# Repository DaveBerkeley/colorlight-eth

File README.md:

ColorLight Ethernet Interface
====

This PCB provides the RJ45 and magnetics to connect a pair of Ethernet sockets to the 
[Colorlight i9](https://github.com/wuxx/Colorlight-FPGA-Projects/blob/master/colorlight_i9_v7.2.md)
FPGA dev board.

I'm using the excellent [LiteX](https://github.com/enjoy-digital/litex) SoC builder from [Enjoy Digital](http://www.enjoy-digital.fr/).

This uses the 
[liteeth](https://github.com/enjoy-digital/liteeth)
library to create the MAC and interface to the PHY.

The dev board contains a pair of Broadcom 
[B50612D](https://github.com/wuxx/Colorlight-FPGA-Projects/blob/master/doc/B50612D-datasheet.pdf)
Gigabit Ethernet Transceivers.

The project was inspired by this [Ethernet interface](https://github.com/kazkojima/colorlight-i5-tips#ethernet) by kazkojima.

I found an 
[RJ45 connecter](https://www.digikey.co.uk/en/products/detail/trp-connector-b-v/2250013-4/9451594)
with built in magnetics, which makes the whole design a lot simpler.

I've got the system loading a binary image over TFTP and booting. I've not yet had time to do any more tests.

The edge connector does not have LED outputs on it unfortunately. 
So I've wired these to a 5-pin header on the side of the board.
There are 4 resistors on the back of the board to limit the current through the LEDs.
The LEDs in these sockets are bicolour bidirectional, but only one direction is supported.

There is also a jumper to select between 5V and 3V3 connection to the pulse transformers, 
but the circuit seems to work without this being conencted to either. 
I need to look into its purpose.

I'm currently running [PanglOS](https://github.com/DaveBerkeley/panglos) on the RISC-V.
This doesn't yet have a scheduler on the RISC-V, so I don't have any multitasking.
Software for the Ethernet interface on my board is still work in progess.

            __   _ __      _  __
           / /  (_) /____ | |/_/
          / /__/ / __/ -_)>  <
         /____/_/\__/\__/_/|_|
       Build your hardware, easily!

     (c) Copyright 2012-2024 Enjoy-Digital
     (c) Copyright 2007-2015 M-Labs

     BIOS built on Oct 19 2024 10:06:09
     BIOS CRC passed (bfabfcc0)

     LiteX git sha1: a59b67e4

    --=============== SoC ==================--
    CPU:            VexRiscv_LinuxDebug @ 50MHz
    BUS:            wishbone 32-bit @ 4GiB
    CSR:            32-bit data
    ROM:            128.0KiB
    SRAM:           8.0KiB
    L2:             8.0KiB
    FLASH:          8.0MiB
    SDRAM:          8.0MiB 32-bit @ 50MT/s (CL-2 CWL-2)
    MAIN-RAM:       8.0MiB

    --========== Initialization ============--
    Ethernet init...
    Initializing SDRAM @0x40000000...
    Switching SDRAM to software control.
    Switching SDRAM to hardware control.
    Memtest at 0x40000000 (2.0MiB)...
      Write: 0x40000000-0x40200000 2.0MiB     
       Read: 0x40000000-0x40200000 2.0MiB     
    Memtest OK
    Memspeed at 0x40000000 (Sequential, 2.0MiB)...
      Write speed: 18.4MiB/s
       Read speed: 25.3MiB/s

    Initializing w25q64 SPI Flash @0x00800000...
    SPI Flash clk configured to 25 MHz
    Memspeed at 0x800000 (Sequential, 4.0KiB)...
       Read speed: 2.3MiB/s
    Memspeed at 0x800000 (Random, 4.0KiB)...
       Read speed: 1.0MiB/s

    --============== Boot ==================--
    Booting from serial...
    Press Q or ESC to abort boot completely.
    sL5DdSMmkekro
                 Timeout
    Booting from flash...
    Error: Invalid image length 0xacc0d000
    Booting from network...
    Local IP: 192.168.0.249
    Remote IP: 192.168.0.189
    Booting from boot.json...
    Copying app.bin to 0x40000000... (109760 bytes)
    Executing booted program at 0x40000000

    --============= Liftoff! ===============--
     ____                   _  ___  ____  
    |  _ \ __ _ _ __   __ _| |/ _ \/ ___| 
    | |_) / _` | '_ \ / _` | | | | \___ \ 
    |  __/ (_| | | | | (_| | | |_| |___) |
    |_|   \__,_|_| |_|\__, |_|\___/|____/ 
                      |___/               

    LiteX/PanglOS. Built Oct 19 2024 09:49:13

    1049893 main DEBUG main.cpp +641 app_main() :

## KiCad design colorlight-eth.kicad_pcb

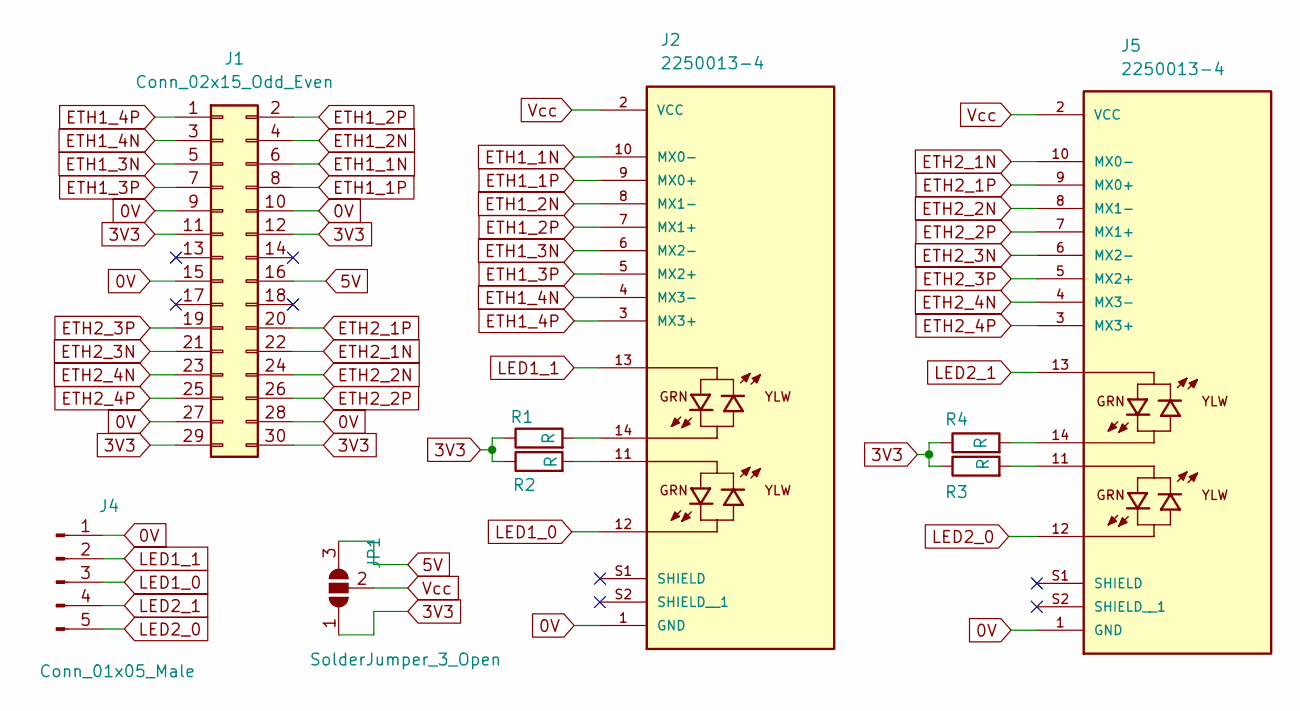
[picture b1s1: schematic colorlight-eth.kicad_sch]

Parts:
J1: Conn_02x15_Odd_Even; PinHeader_2x15_P2.54mm_Vertical
J2, J5: 2250013-4; BEL_2250013-4; PARTREV 2
J4: Conn_01x05_Male; PinHeader_1x05_P2.54mm_Vertical
JP1: SolderJumper_3_Open; SolderJumper-3_P1.3mm_Open_RoundedPad1.0x1.5mm
R1, R2, R3, R4: R; R_0603_1608Metric

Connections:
0V: J1.9, J1.10, J1.15, J1.27, J1.28, J2.1 (GND), J4.1, J5.1 (GND)
3V3: J1.11, J1.12, J1.29, J1.30, JP1.1 (A), R1.1, R2.1, R3.1, R4.1
5V: J1.16, JP1.3 (B)
ETH1_1N: J1.6, J2.10 (MX0-)
ETH1_1P: J1.8, J2.9 (MX0+)
ETH1_2N: J1.4, J2.8 (MX1-)
ETH1_2P: J1.2, J2.7 (MX1+)
ETH1_3N: J1.5, J2.6 (MX2-)
ETH1_3P: J1.7, J2.5 (MX2+)
ETH1_4N: J1.3, J2.4 (MX3-)
ETH1_4P: J1.1, J2.3 (MX3+)
ETH2_1N: J1.22, J5.10 (MX0-)
ETH2_1P: J1.20, J5.9 (MX0+)
ETH2_2N: J1.24, J5.8 (MX1-)
ETH2_2P: J1.26, J5.7 (MX1+)
ETH2_3N: J1.21, J5.6 (MX2-)
ETH2_3P: J1.19, J5.5 (MX2+)
ETH2_4N: J1.23, J5.4 (MX3-)
ETH2_4P: J1.25, J5.3 (MX3+)
LED1_0: J2.12, J4.3
LED1_1: J2.13, J4.2
LED2_0: J4.5, J5.12
LED2_1: J4.4, J5.13
unnamed: J2.11, R2.2
unnamed: J2.14, R1.2
unnamed: J5.11, R3.2
unnamed: J5.14, R4.2
Vcc: J2.2 (VCC), J5.2 (VCC), JP1.2 (C)

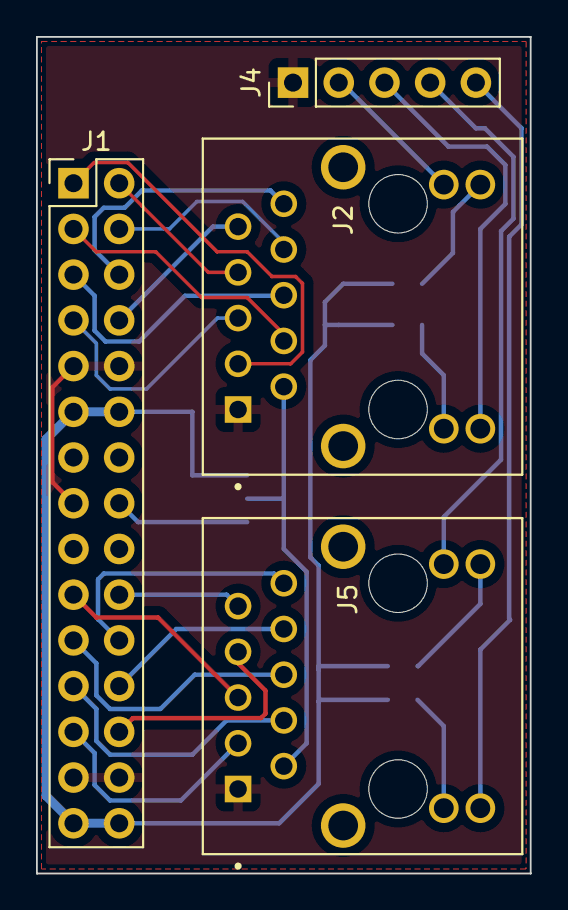
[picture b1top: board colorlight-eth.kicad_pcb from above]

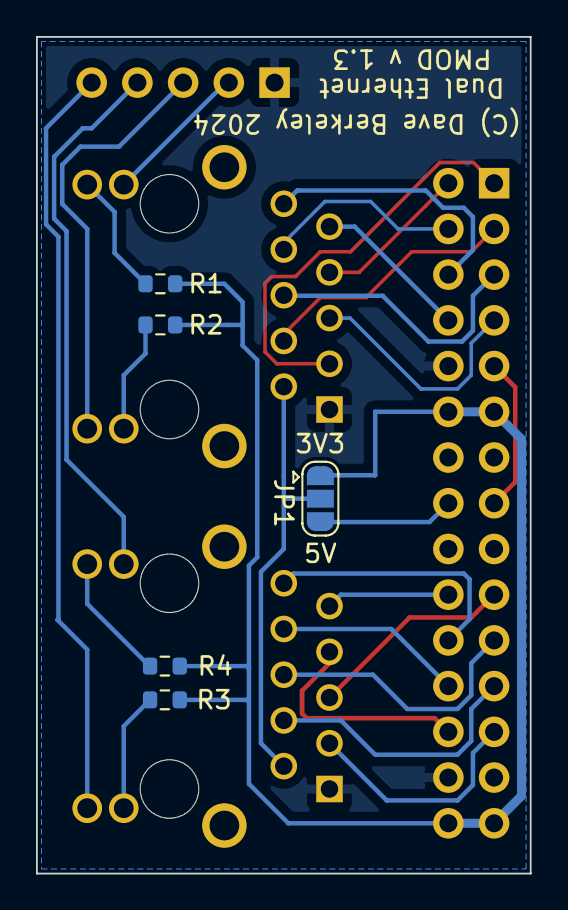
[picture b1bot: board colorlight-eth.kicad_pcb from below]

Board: 2 copper layers, 27.4 x 46.5 mm, 9 parts (5 on the bottom side), 28 nets.

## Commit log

2024-09-13 init
2024-09-13 v 1.1 : resistors on the back
2024-09-13 v1.2 : fix 5V feed to magnetics
2024-09-28 v 1.3 : mirrored connector pins
2024-10-19 deleted faulty v 1.0 pcb
2024-10-19 Added README
2024-10-19 Added PCB image
2024-10-20 Add word FPGA to readme
2024-10-21 more text to README
